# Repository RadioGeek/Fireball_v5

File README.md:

# Fireball_v5

<B>Compiling the Code</B>
<p>The Arduino IDE to compile and upload the code to the Fireball.  I've used the older v1.0.6 and latest
(current as of today) v1.6.8 IDE.  You will need to add the following board manager URL in the Arduino IDE Preferences, 
in order to successfully compile for the Atmel ATtiny85 processor:
https://raw.githubusercontent.com/damellis/attiny/ide-1.6.x-boards-manager/package_damellis_attiny_index.json

After you have added this to the board manager, goto Tools -> Board:, and select ATtiny at the bottom of the pulldown.
Then select the Tools menu again and you'll see additional options for Processor & Clock.
  Under the Tools -> Processor:, select ATtiny85.
  Under the Tools -> Clock:, select 8 MHz (internal)

Click the Verify button to confirm the code will compile.  If it does, you're ready to connect your AVR Programmer and
compile/upload the code.  I'm using an AVRISP mkII programmer, but I've also found my cheaper USBtinyISP purchased off
ebay worked just fine.  Sometimes you might have to select the Upload Using Programmer method, if the normal method fails.

DON'T FORGET TO BURN THE BOOTLOADER <B>BEFORE</B> UPLOADING THE CODE.</p>

<b>Config.h Settings</b>

<p>There are 3 lines in the config.h file that should be set based on user preference.</p>
<p>#define IDLE_BEEPS       true  // Enable short beeps on the second during idle time.  Set to either true or false. </p>
<p>#define SEND_CALL        true  // Enables sending of your callsign.  Set to either true or false. </p>
<p>#define CALLSIGN        "FB5"  // Operator's callsign.  Self explanatory, but can be anything less than 15 characters. </p>

<p> Have Fun with it!!!<p/>

John
AB5SS

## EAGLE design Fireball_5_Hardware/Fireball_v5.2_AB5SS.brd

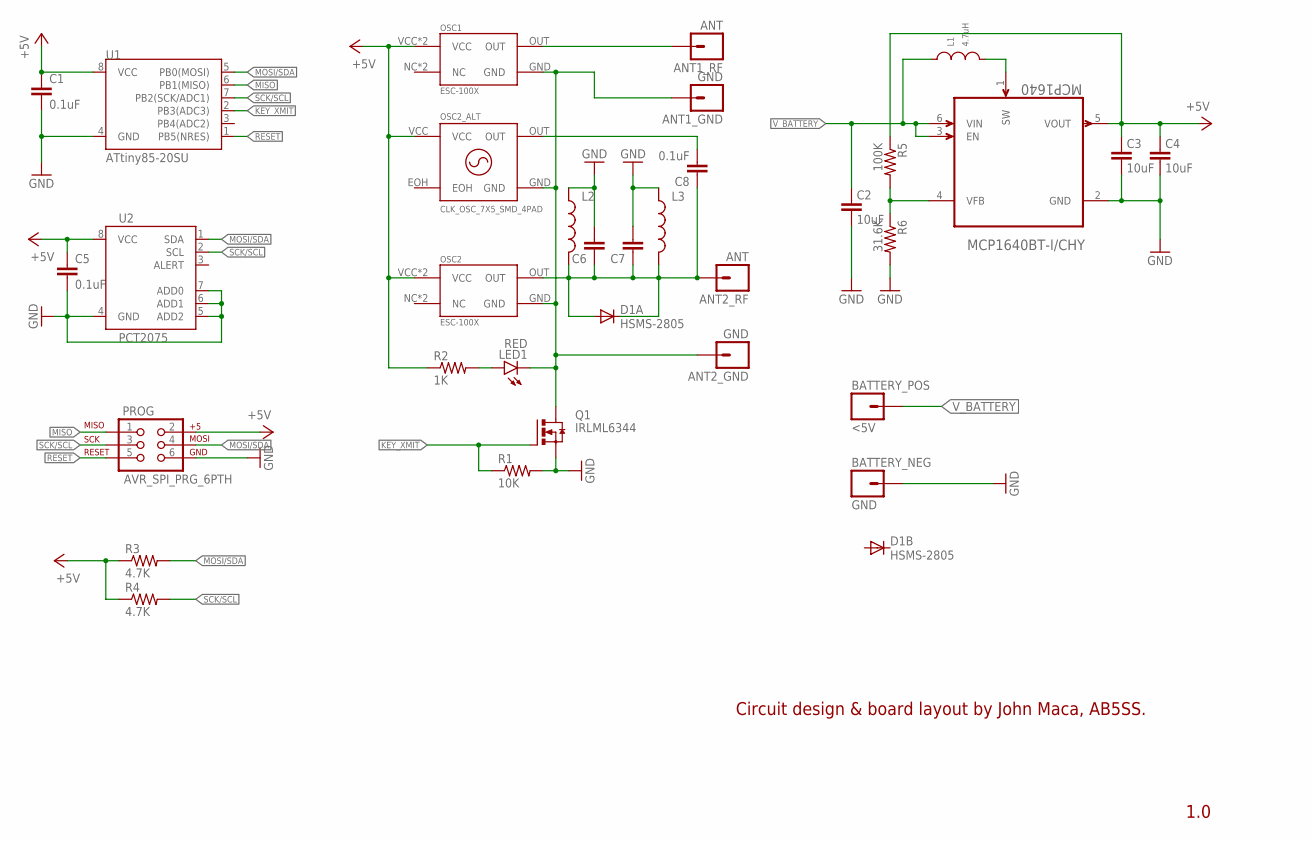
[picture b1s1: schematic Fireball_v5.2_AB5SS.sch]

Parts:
ANT1_GND, ANT2_GND: GND; 1X01_LONGPAD
ANT1_RF, ANT2_RF: ANT; 1X01_LONGPAD
BATTERY_NEG: GND; 1X01_LONGPAD
BATTERY_POS: <5V; 1X01_LONGPAD
C1, C5: 0.1uF; 0603-CAP
C2, C3, C4: 10uF; C603
C6, C7: CAP0402-CAP; 0402-CAP
C8: 0.1uF; 0402-CAP
D1: HSMS-2805; SOT143_AVAGO
L1: 4.7uH; SRN4026
L2, L3: INDUCTOR0402; C0402
LED1: RED; LED-0603
MCP1640: MCP1640BT-I/CHY; SOT95P270X145-6N
OSC1, OSC2: ESC-100X; OSC-20.86X13.2-4PIN
OSC2_ALT: CLK_OSC_7X5_SMD_4PAD; CLK_OSC_7.00X5.00_SMD-4PAD
PROG: AVR_SPI_PRG_6PTH; 2X3
Q1: IRLML6344; MICRO3
R1: 10K; 0603-RES
R2: 1K; 0603-RES
R3, R4: 4.7K; 0603-RES
R5: 100K; 0603-RES
R6: 31.6K; 0603-RES
U1: ATtiny85-20SU; SO08-EIAJ
U2: PCT2075; SO08

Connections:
+5V: C1.1, C3.1, C4.1, C5.1, MCP1640.5 (VOUT), OSC1.VCC, OSC1.VCC2 (VCC), OSC2.VCC, OSC2.VCC2 (VCC), OSC2_ALT.VCC, PROG.2, R2.1, R3.1, R4.1, R5.1, U1.8 (VCC), U2.8 (VCC)
GND: BATTERY_NEG.1, C1.2, C2.2, C3.2, C4.2, C5.2, C6.2, C7.2, L2.1, L3.1, MCP1640.2 (GND), PROG.6, Q1.2 (S), R1.2, R6.2, U1.4 (GND), U2.4 (GND), U2.5 (ADD2), U2.6 (ADD1), U2.7 (ADD0)
KEY_XMIT: Q1.1 (G), R1.1, U1.2 (PB3(ADC3))
L1_SW: L1.P$2 (2), MCP1640.1 (SW)
MISO: PROG.1, U1.6 (PB1(MISO))
MOSI/SDA: PROG.4, R3.2, U1.5 (PB0(MOSI)), U2.1 (SDA)
unnamed: ANT1_GND.1, ANT2_GND.1, LED1.C, OSC1.GND, OSC2.GND, OSC2_ALT.GND, Q1.3 (D)
unnamed: MCP1640.4 (VFB), R5.2, R6.1
unnamed: LED1.A, R2.2
unnamed: ANT1_RF.1, OSC1.OUT
unnamed: ANT2_RF.1, C6.1, C7.1, C8.1, D1.1 (C), D1.3 (A), L2.2, L3.2, OSC2.OUT
unnamed: C8.2, OSC2_ALT.OUT
RESET: PROG.5, U1.1 (PB5(NRES))
SCK/SCL: PROG.3, R4.2, U1.7 (PB2(SCK/ADC1)), U2.2 (SCL)
V_BATTERY: BATTERY_POS.1, C2.1, L1.P$1 (1), MCP1640.3 (EN), MCP1640.6 (VIN)

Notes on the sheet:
1.0
Circuit design & board layout by John Maca, AB5SS.

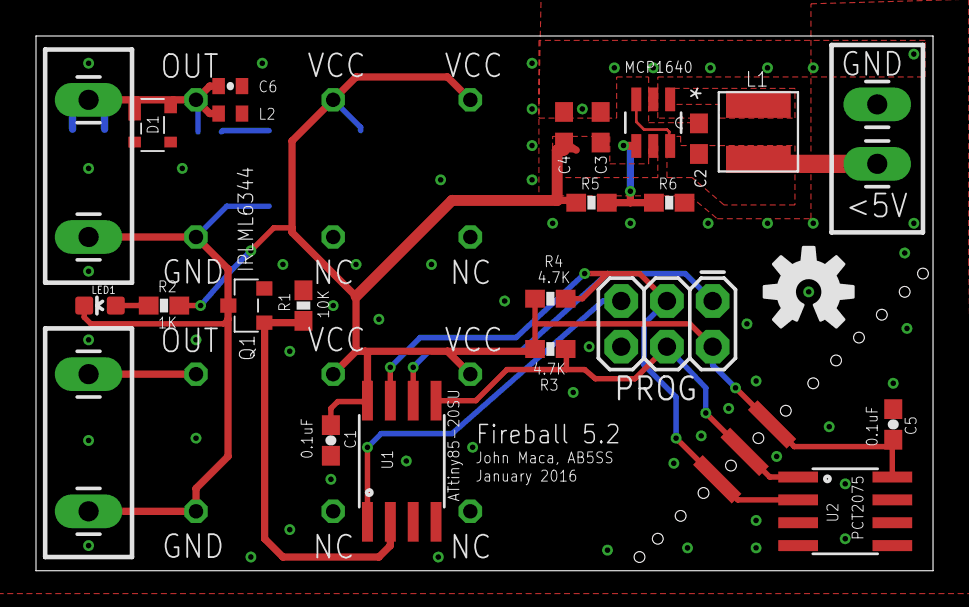
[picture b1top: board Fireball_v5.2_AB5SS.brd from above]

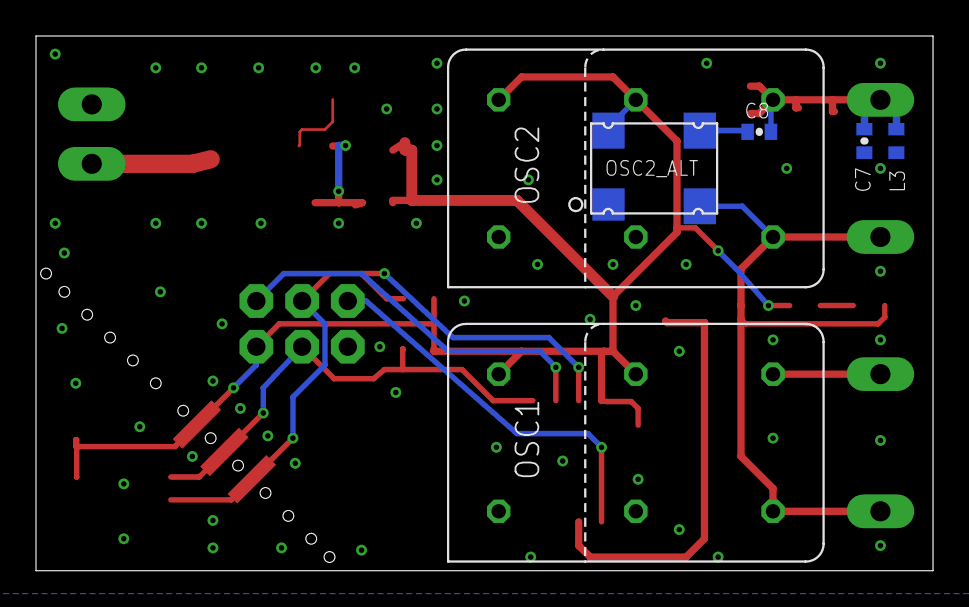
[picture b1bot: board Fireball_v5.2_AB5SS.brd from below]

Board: 2 copper layers, 49.8 x 29.7 mm, 34 parts (6 on the bottom side), 15 nets.

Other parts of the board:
U$1: OSHW-LOGO-M

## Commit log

2015-12-07 Fireball v5 Transmitter
    The Fireball v5 is transmits the temperature in C & F in Morse code.
2016-04-14 config update
    Minor updates to config.h file
2016-05-30 Merge branch 'master' into config-update
    Major change to add hardware files, including the EagleCAD 7 Gerber
    files. Also the design & part values for the 72 to 144 MHz doubler.

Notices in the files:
parts and their libraries:
SparkFun-Connectors: Licensing: Creative Commons ShareAlike 4.0 International - https://creativecommons.org/licenses/by-sa/4.0
